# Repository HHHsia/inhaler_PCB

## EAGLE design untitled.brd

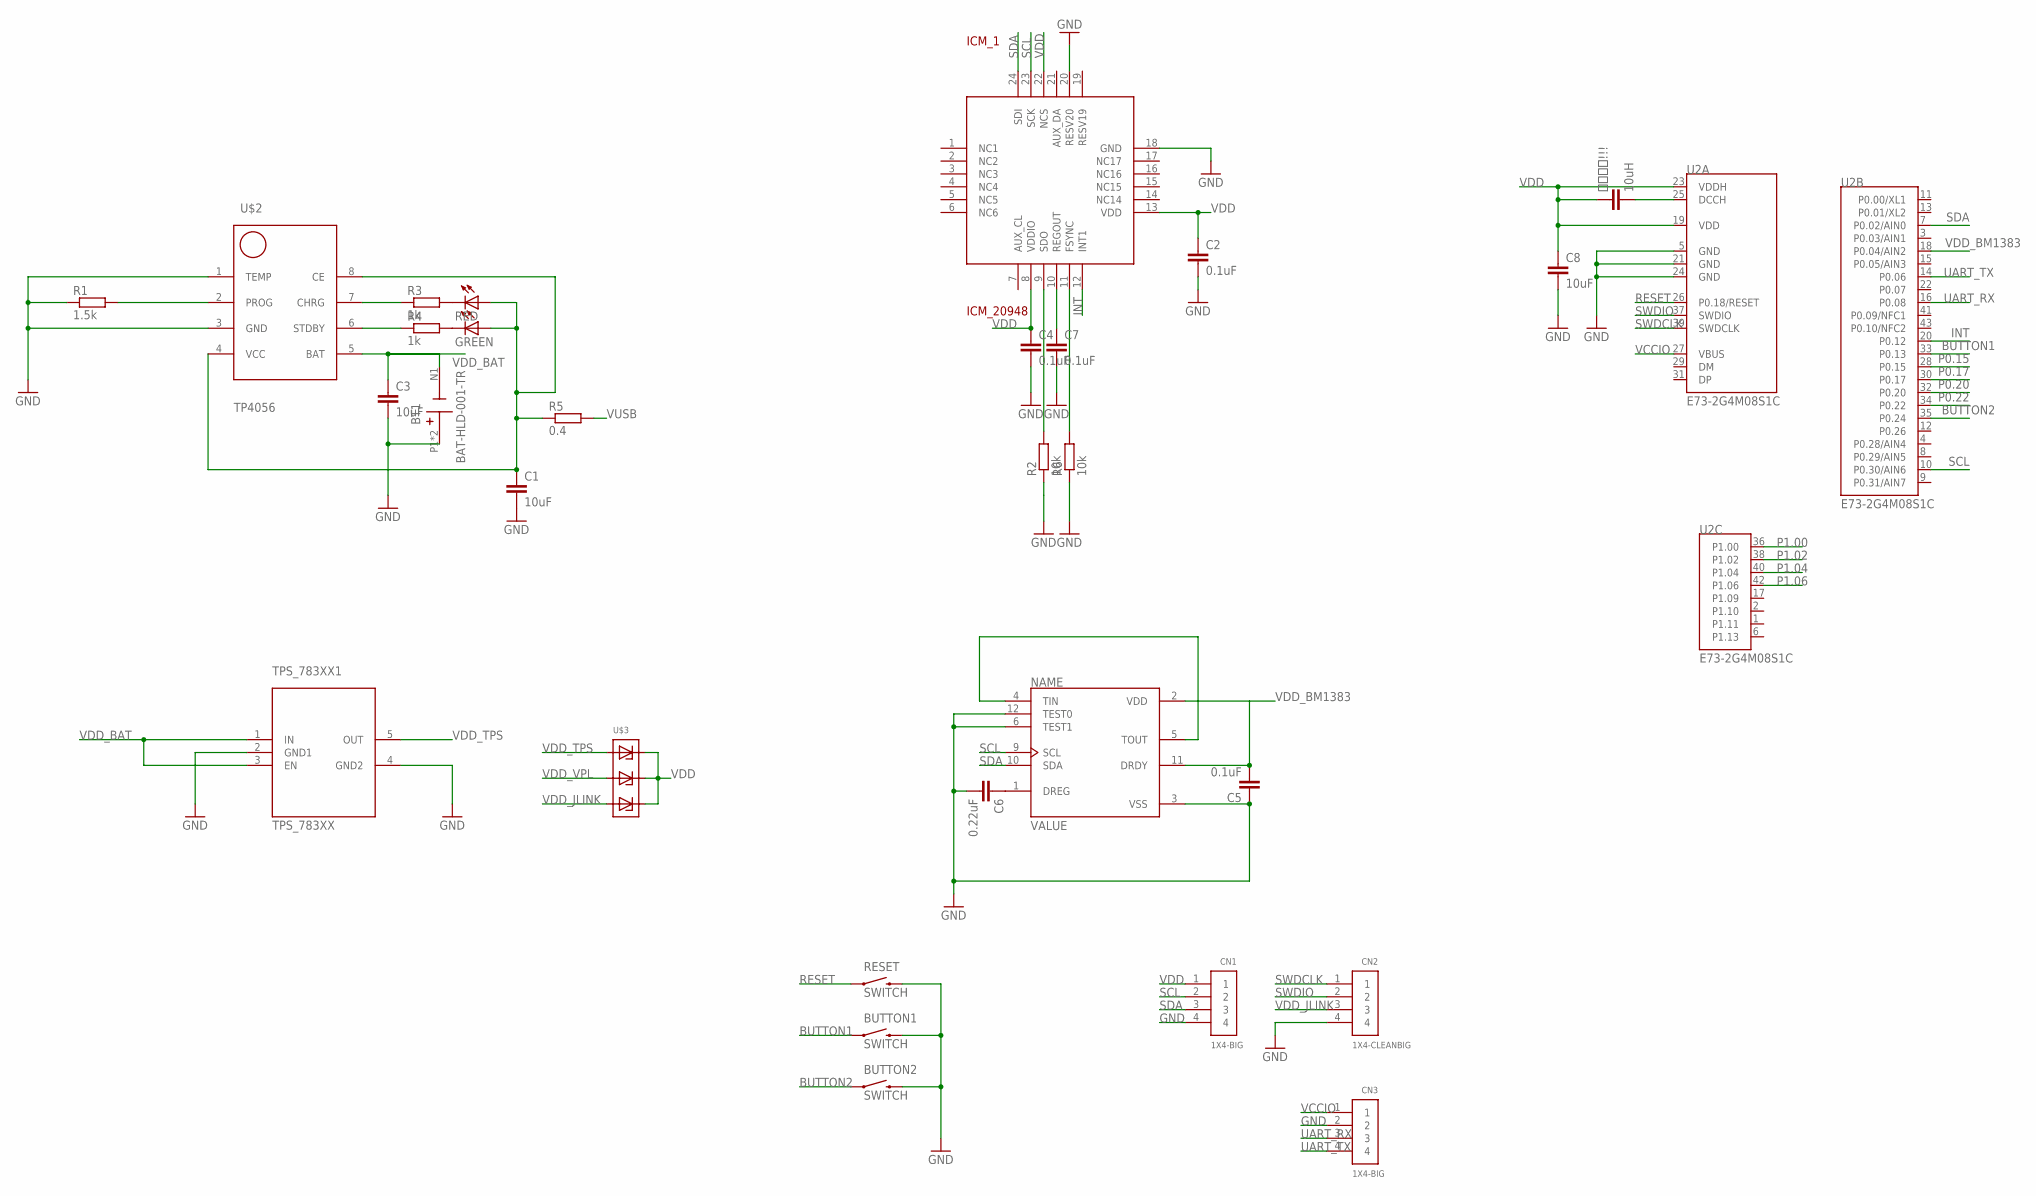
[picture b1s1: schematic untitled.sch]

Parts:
BT1: BAT-HLD-001-TR; BAT_BAT-HLD-001-TR
BUTTON1, BUTTON2: SWITCH; SWITCH_2PIN
C1, C3, C8: 10uF; C0805
C2, C4, C5, C7: 0.1uF; C0805
C6: 0.22uF; C0805
CN1, CN3: 1X4-BIG; 1X04-BIG
CN2: 1X4-CLEANBIG; 1X04-CLEANBIG
GREEN: LED_E; LED_1206
ICM_1: ICM_20948; QFN40P300X300X105-25N
R1: 1.5k; R0805
R2, R6: 10k; R0805
R3, R4: 1k; R0805
R5: 0.4; R0805
RED: LED_E; LED_1206
RESET: SWITCH; SWITCH_2PIN
TPS_783XX1: TPS_783XX; SOT65P280X145-5N
U1: BM1383AGLV-ZE2; PQFN55P250X250X100-12N
U2: E73-2G4M08S1C
U$2: TP4056; SOP8
U$3: SD103ATW; SOT363
這是電感!!!: 10uH; C0805

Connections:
BUTTON1: BUTTON1.1, U2.33 (P0.13)
BUTTON2: BUTTON2.1, U2.35 (P0.24)
GND: BT1.P1 (+), BT1.P2 (+), BUTTON1.2, BUTTON2.2, C1.2, C2.2, C3.2, C4.2, C5.1, C6.2, C7.2, C8.2, CN1.4, CN2.4, CN3.2, ICM_1.18 (GND), ICM_1.20 (RESV20), R1.1, R2.1, R6.1, RESET.2, TPS_783XX1.2 (GND1), TPS_783XX1.4 (GND2), U1.3 (VSS), U1.6 (TEST1), U1.12 (TEST0), U2.5 (GND), U2.21 (GND), U2.24 (GND), U$2.1 (TEMP), U$2.3 (GND)
INT: ICM_1.12 (INT1), U2.20 (P0.12)
unnamed: R1.2, U$2.2 (PROG)
unnamed: GREEN.C, R4.2
unnamed: R3.1, U$2.7 (CHRG)
unnamed: R3.2, RED.C
unnamed: R4.1, U$2.6 (STDBY)
unnamed: C1.1, GREEN.A, R5.1, RED.A, U$2.4 (VCC), U$2.8 (CE)
unnamed: U1.4 (TIN), U1.5 (TOUT)
unnamed: C6.1, U1.1 (DREG)
unnamed: U2.25 (DCCH), 這是電感!!!.2
unnamed: ICM_1.9 (SDO), R2.2
unnamed: C7.1, ICM_1.10 (REGOUT)
unnamed: ICM_1.11 (FSYNC), R6.2
P0.15: U2.28 (P0.15)
P0.17: U2.30 (P0.17)
P0.20: U2.32 (P0.20)
P0.22: U2.34 (P0.22)
P1.00: U2.36 (P1.00)
P1.02: U2.38 (P1.02)
P1.04: U2.40 (P1.04)
P1.06: U2.42 (P1.06)
RESET: RESET.1, U2.26 (P0.18/RESET)
SCL: CN1.2, ICM_1.23 (SCK), U1.9 (SCL), U2.10 (P0.30/AIN6)
SDA: CN1.3, ICM_1.24 (SDI), U1.10 (SDA), U2.7 (P0.02/AIN0)
SWDCLK: CN2.1, U2.39 (SWDCLK)
SWDIO: CN2.2, U2.37 (SWDIO)
UART_RX: CN3.3, U2.16 (P0.08)
UART_TX: CN3.4, U2.14 (P0.06)
VCCIO: CN3.1, U2.27 (VBUS)
VDD: C2.1, C4.1, C8.1, CN1.1, ICM_1.8 (VDDIO), ICM_1.13 (VDD), ICM_1.22 (NCS), U2.19 (VDD), U2.23 (VDDH), U$3.2, U$3.4, U$3.6, 這是電感!!!.1
VDD_BAT: BT1.N1 (-), C3.1, TPS_783XX1.1 (IN), TPS_783XX1.3 (EN), U$2.5 (BAT)
VDD_BM1383: C5.2, U1.2 (VDD), U1.11 (DRDY), U2.18 (P0.04/AIN2)
VDD_JLINK: CN2.3, U$3.5
VDD_TPS: TPS_783XX1.5 (OUT), U$3.1
VDD_VPL: U$3.3
VUSB: R5.2

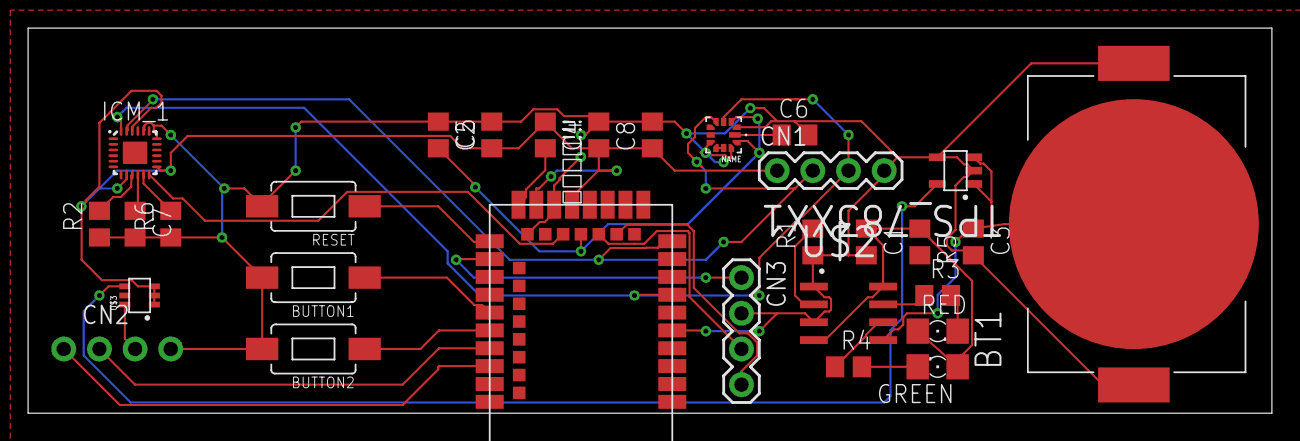
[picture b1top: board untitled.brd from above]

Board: 2 copper layers, 88.6 x 27.4 mm, 30 parts (0 on the bottom side), 29 nets.
